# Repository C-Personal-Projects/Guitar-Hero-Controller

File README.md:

# Guitar Hero Project
This is a repository for a guitar hero controller that is compatible with Windows computers. It is 3D printed, powered by an Arduino Leonardo, and connects to the computer through a USB cable. This project involves the use of a PCB that allows the frets to light up in their respective colors when they are pressed.

### Picture of Guitar

### Picture of PCB

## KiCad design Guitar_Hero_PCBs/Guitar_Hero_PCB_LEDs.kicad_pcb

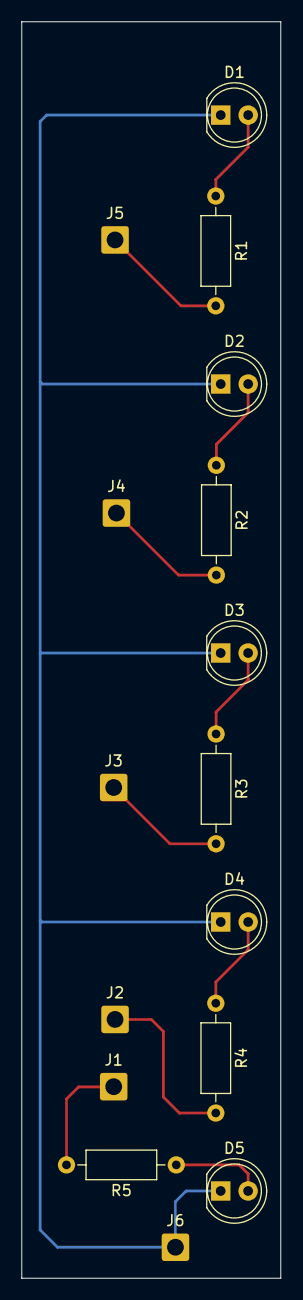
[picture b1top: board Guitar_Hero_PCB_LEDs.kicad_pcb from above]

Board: 2 copper layers, 24.0 x 116.3 mm, 16 parts (0 on the bottom side), 11 nets.

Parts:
D1, D2, D3, D4, D5: LED; LED_D5.0mm
J1, J2, J3, J4, J5, J6: Conn_01x01; SolderWire-0.75sqmm_1x01_D1.25mm_OD2.3mm
R1, R2, R3, R4, R5: R_US; R_Axial_DIN0207_L6.3mm_D2.5mm_P10.16mm_Horizontal

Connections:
unnamed: D1.2 (A), R1.1
unnamed: D1.1 (K), D2.1 (K), D3.1 (K), D4.1 (K), D5.1 (K), J6.1
unnamed: D2.2 (A), R2.1
unnamed: D3.2 (A), R3.1
unnamed: D4.2 (A), R4.1
unnamed: D5.2 (A), R5.1
unnamed: J1.1, R5.2
unnamed: J2.1, R4.2
unnamed: J3.1, R3.2
unnamed: J4.1, R2.2
unnamed: J5.1, R1.2

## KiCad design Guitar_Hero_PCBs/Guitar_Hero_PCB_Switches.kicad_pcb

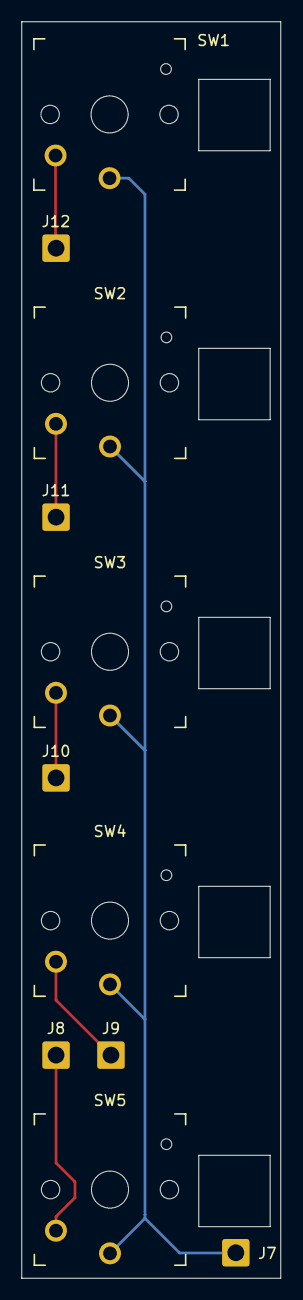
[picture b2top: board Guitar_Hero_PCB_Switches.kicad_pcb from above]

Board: 2 copper layers, 23.9 x 116.2 mm, 11 parts (0 on the bottom side), 6 nets.

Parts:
J7, J8, J9, J10, J11, J12: Conn_01x01; SolderWire-0.75sqmm_1x01_D1.25mm_OD2.3mm
SW1, SW2, SW3, SW4, SW5: SW_SPST; SW_PG1350

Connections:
unnamed: J7.1, SW1.1 (A), SW2.1 (A), SW3.1 (A), SW4.1 (A), SW5.1 (A)
unnamed: J8.1, SW5.2 (B)
unnamed: J9.1, SW4.2 (B)
unnamed: J10.1, SW3.2 (B)
unnamed: J11.1, SW2.2 (B)
unnamed: J12.1, SW1.2 (B)

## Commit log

2026-02-09 Add Pictures

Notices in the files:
Guitar_Hero_PCBs/Guitar_Hero_PCB_LEDs.kicad_pcb:
creativecommons.org/licenses/by/4.0
License: CC BY 4.0
